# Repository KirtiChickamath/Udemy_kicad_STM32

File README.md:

# STM32 
This project is a simple STM32 based board designed as part of learning and practicing KiCad.It is built around STM32F103C8T6 microcontroller and includes USB input, regulated to 3.3V supply using AMS1117
## Project Details

**Project Name:** STM32 board

**Software Used:** KiCad

**Learning Source** Learn KiCad V6 and STM32 Hardware Design from Udemy

## Images

### Schematic

### PCB Layout

### 3D

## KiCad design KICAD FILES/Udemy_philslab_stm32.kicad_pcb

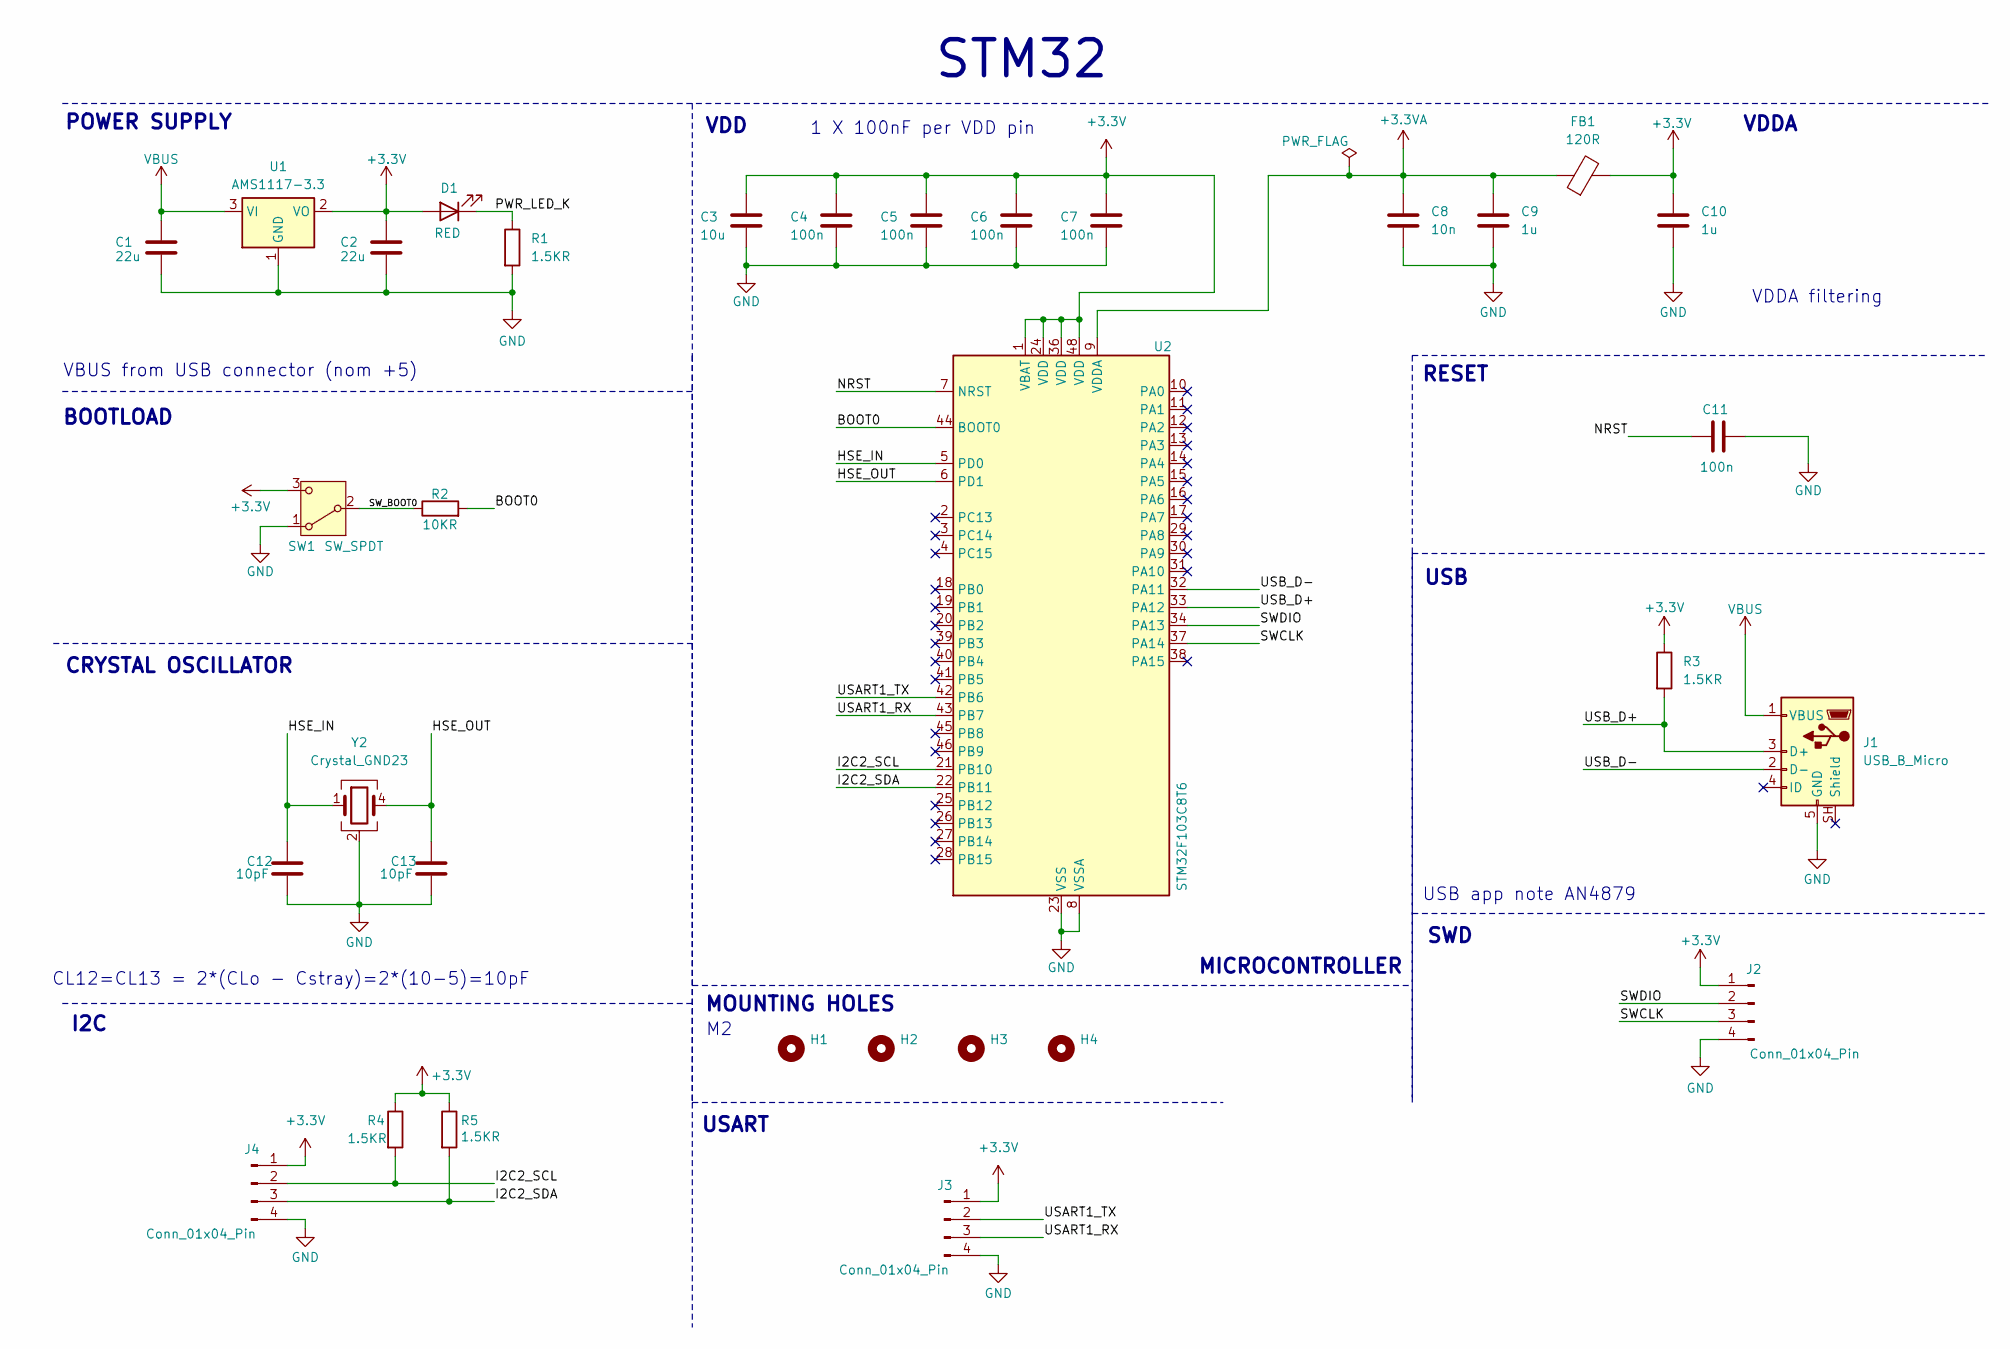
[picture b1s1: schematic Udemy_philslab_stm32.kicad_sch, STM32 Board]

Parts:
C1, C2: 22u; C_0805_2012Metric
C3: 10u; C_0603_1608Metric
C4, C5, C6, C7, C11: 100n; C_0402_1005Metric
C8: 10n; C_0402_1005Metric
C9, C10: 1u; C_0402_1005Metric
C12, C13: 10pF; C_0402_1005Metric
D1: RED; LED_0603_1608Metric
FB1: 120R; L_0603_1608Metric
H1, H2, H3, H4: MountingHole; MountingHole_2.2mm_M2
J1: USB_B_Micro; USB_Micro-B_Wuerth_629105150521
J2, J3, J4: Conn_01x04_Pin; PinHeader_1x04_P2.54mm_Vertical
R1, R3, R4, R5: 1.5KR; R_0402_1005Metric
R2: 10KR; R_0402_1005Metric
SW1: SW_SPDT; SW_SPDT_PCM12
U1: AMS1117-3.3; SOT-223-3_TabPin2
U2: STM32F103C8T6; LQFP-48_7x7mm_P0.5mm
Y2: Crystal_GND23; Crystal_SMD_3225-4Pin_3.2x2.5mm

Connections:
+3.3V: C2.1, C3.1, C4.1, C5.1, C6.1, C7.1, C10.1, D1.2 (A), FB1.2, J2.1, J3.1, J4.1, R3.1, R4.1, R5.1, SW1.3 (C), U1.2 (VO), U2.1 (VBAT), U2.24 (VDD), U2.36 (VDD), U2.48 (VDD)
+3.3VA: C8.1, C9.1, FB1.1, U2.9 (VDDA)
/BOOT0: R2.2, U2.44 (BOOT0)
/HSE_IN: C12.1, U2.5 (PD0), Y2.1
/HSE_OUT: C13.1, U2.6 (PD1), Y2.4
/I2C2_SCL: J4.2, R4.2, U2.21 (PB10)
/I2C2_SDA: J4.3, R5.2, U2.22 (PB11)
/NRST: C11.1, U2.7 (NRST)
/PWR_LED_K: D1.1 (K), R1.1
/SWCLK: J2.3, U2.37 (PA14)
/SWDIO: J2.2, U2.34 (PA13)
/SW_BOOT0: R2.1, SW1.2 (B)
/USART1_RX: J3.3, U2.43 (PB7)
/USART1_TX: J3.2, U2.42 (PB6)
/USB_D+: J1.3 (D+), R3.2, U2.33 (PA12)
/USB_D-: J1.2 (D-), U2.32 (PA11)
GND: C1.2, C2.2, C3.2, C4.2, C5.2, C6.2, C7.2, C8.2, C9.2, C10.2, C11.2, C12.2, C13.2, J1.5 (GND), J2.4, J3.4, J4.4, R1.2, SW1.1 (A), U1.1 (GND), U2.8 (VSSA), U2.23 (VSS), U2.35 (VSS), U2.47 (VSS), Y2.2 (G), Y2.3 (G)
VBUS: C1.1, J1.1 (VBUS), U1.3 (VI)

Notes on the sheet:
VDD
SWD
POWER SUPPLY
CRYSTAL OSCILLATOR
USART
USB app note AN4879
CL12=CL13 = 2*(CLo - Cstray)=2*(10-5)=10pF
VDDA
VDDA filtering
RESET
I2C
BOOTLOAD
MOUNTING HOLES
STM32
VBUS from USB connector (nom +5)
USB
MICROCONTROLLER
1 X 100nF per VDD pin

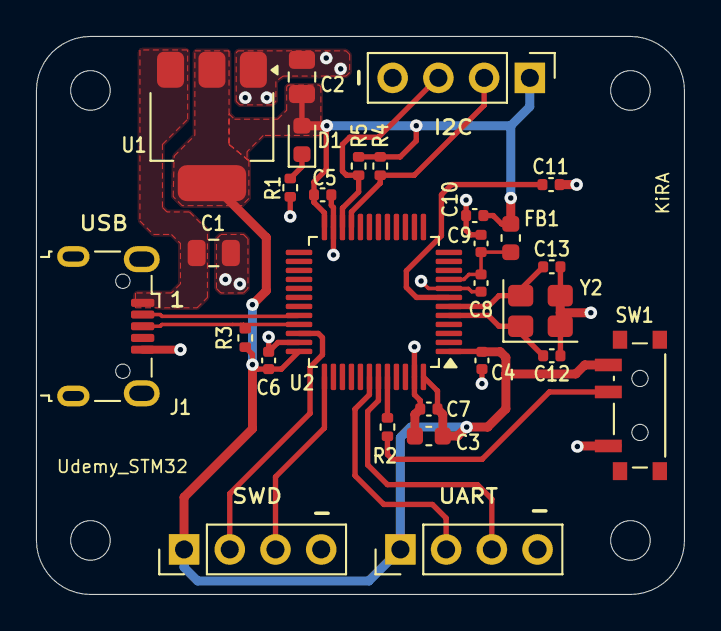
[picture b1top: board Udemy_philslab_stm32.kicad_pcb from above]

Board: 2 copper layers, 36.0 x 31.0 mm, 32 parts (0 on the bottom side), 18 nets.

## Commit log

2026-04-13 Create Manufacturing Files
2026-04-14 README.md
